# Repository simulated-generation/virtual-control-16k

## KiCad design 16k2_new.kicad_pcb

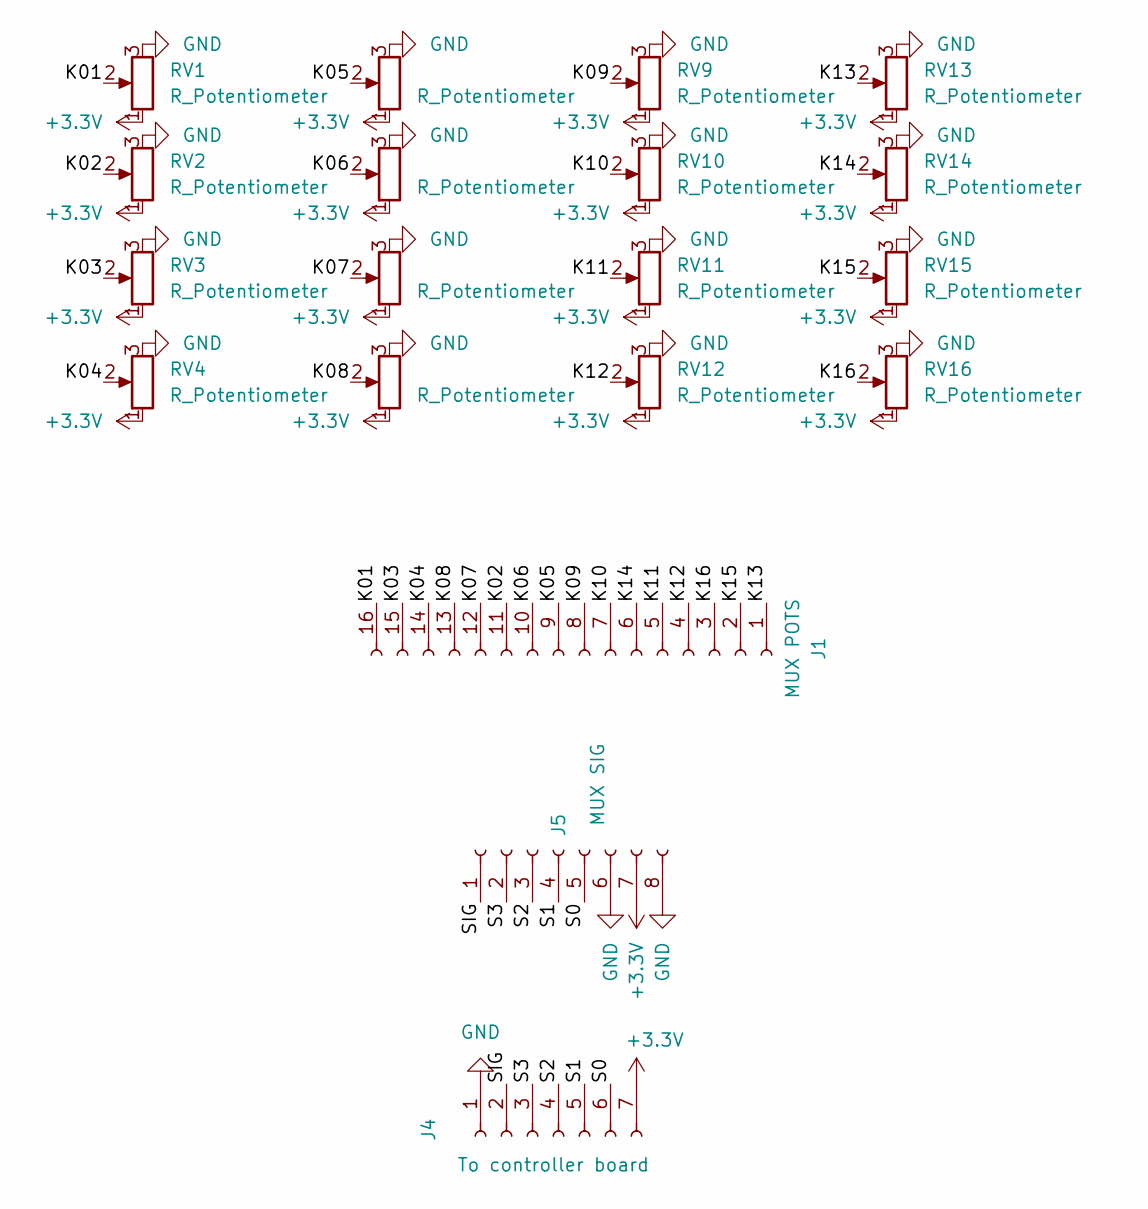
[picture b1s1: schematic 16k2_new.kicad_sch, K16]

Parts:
J1: MUX POTS; PinSocket_1x16_P2.54mm_Vertical
J4: To controller board; JST_XH_B7B-XH-AM_1x07_P2.50mm_Vertical
J5: MUX SIG; PinSocket_1x08_P2.54mm_Vertical
RV1, RV2, RV3, RV4, RV5, RV6, RV7, RV8, RV9, RV10, RV11, RV12, RV13, RV14, RV15, RV16: R_Potentiometer; Potentiometer_Alps_RK09K_Single_Vertical

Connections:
+3.3V: J4.7, J5.7, RV1.1, RV2.1, RV3.1, RV4.1, RV5.1, RV6.1, RV7.1, RV8.1, RV9.1, RV10.1, RV11.1, RV12.1, RV13.1, RV14.1, RV15.1, RV16.1
/K01: J1.16, RV1.2
/K02: J1.11, RV2.2
/K03: J1.15, RV3.2
/K04: J1.14, RV4.2
/K05: J1.9, RV5.2
/K06: J1.10, RV6.2
/K07: J1.12, RV7.2
/K08: J1.13, RV8.2
/K09: J1.8, RV9.2
/K10: J1.7, RV10.2
/K11: J1.5, RV11.2
/K12: J1.4, RV12.2
/K13: J1.1, RV13.2
/K14: J1.6, RV14.2
/K15: J1.2, RV15.2
/K16: J1.3, RV16.2
/S0: J4.6, J5.5
/S1: J4.5, J5.4
/S2: J4.4, J5.3
/S3: J4.3, J5.2
/SIG: J4.2, J5.1
GND: J4.1, J5.6, J5.8, RV1.3, RV2.3, RV3.3, RV4.3, RV5.3, RV6.3, RV7.3, RV8.3, RV9.3, RV10.3, RV11.3, RV12.3, RV13.3, RV14.3, RV15.3, RV16.3

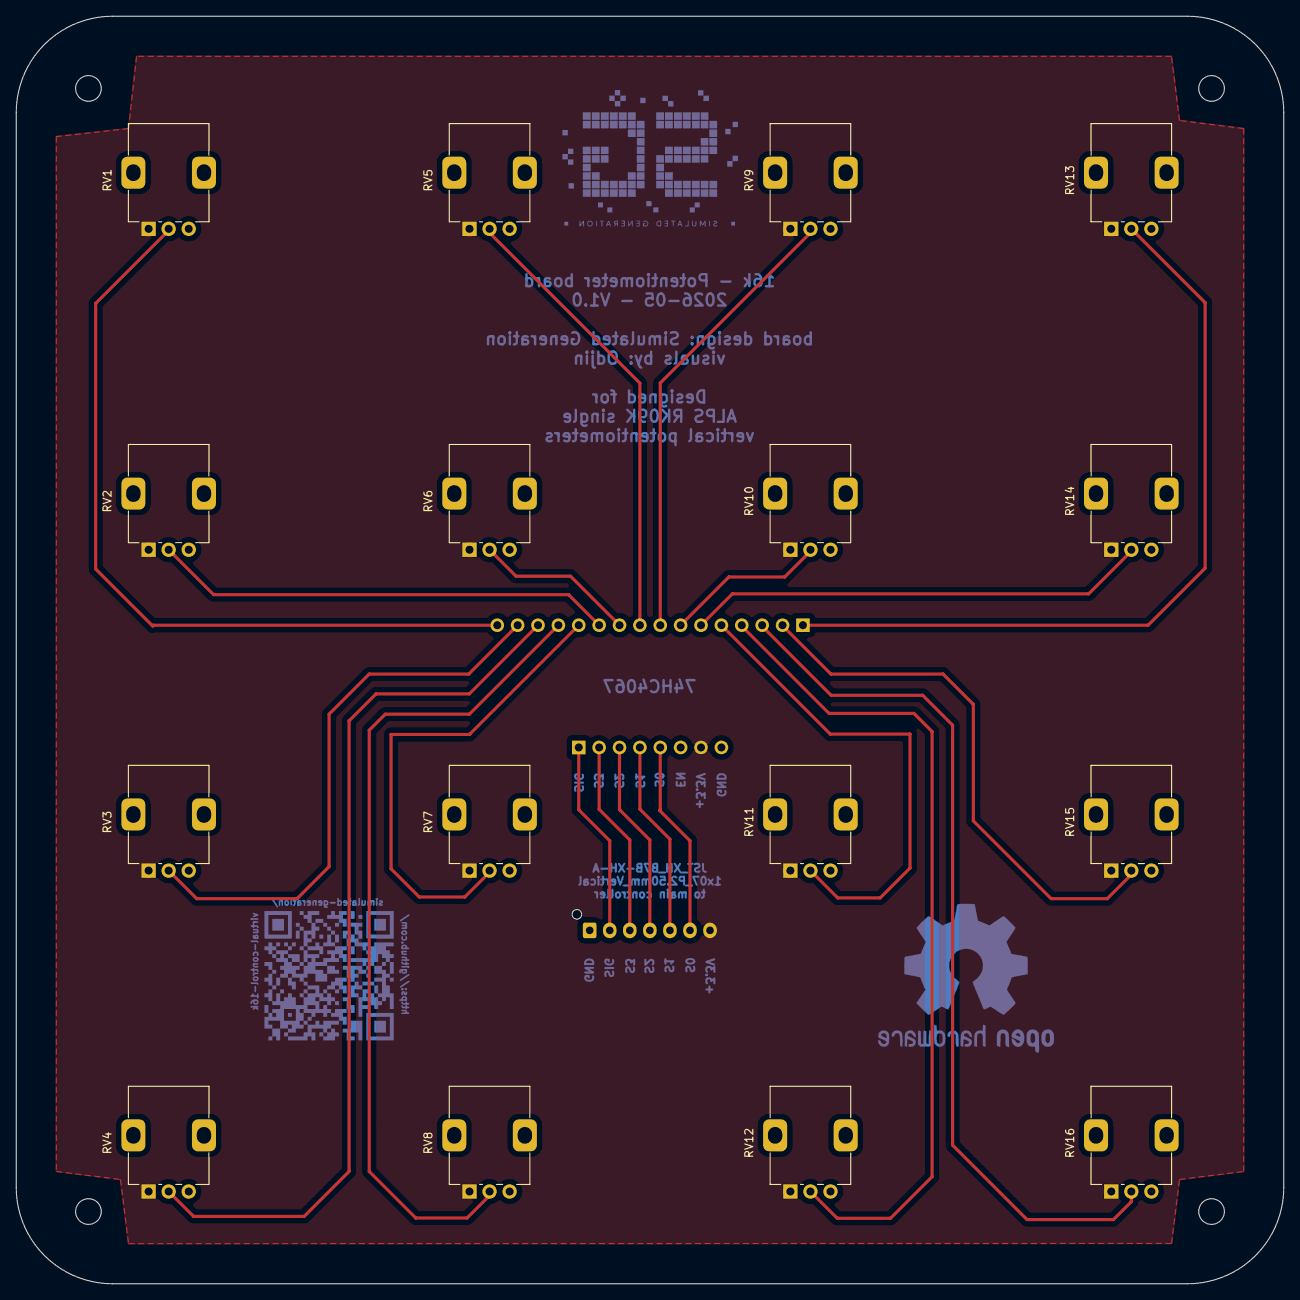
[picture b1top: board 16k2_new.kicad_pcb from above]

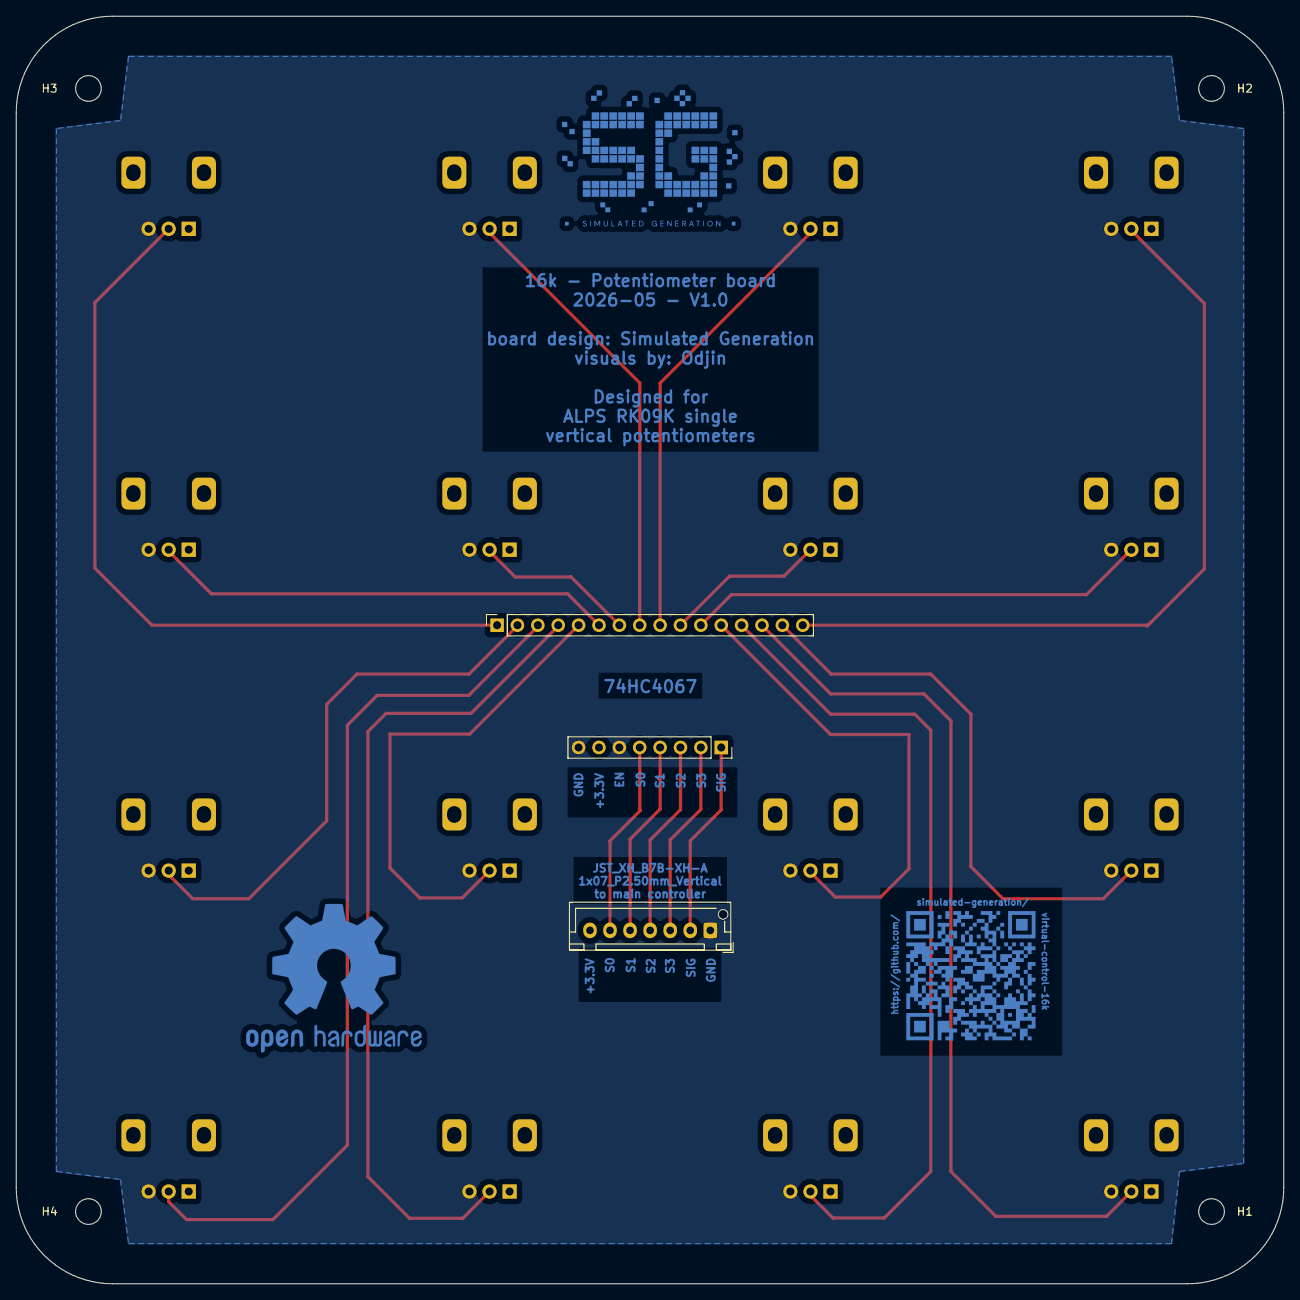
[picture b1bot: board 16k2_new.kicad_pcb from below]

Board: 4 copper layers, 158.0 x 158.0 mm, 23 parts (3 on the bottom side), 23 nets.

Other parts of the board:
H1, H2, H3, H4: MountingHole; MountingHole_3.2mm_M3

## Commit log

2026-05-23 Initial commit of 16 knobs PCB
2026-05-23 Adds MIT licence
2026-05-24 Correct mistakenly removed file from backups
